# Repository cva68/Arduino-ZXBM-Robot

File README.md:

# Arduino ZXBM Robot
Chassis, PCB and Software to create an Arduino robot, including a custom motor driver shield based on the [ZXBM5210 motor driver](https://www.diodes.com/assets/Datasheets/products_inactive_data/ZXBM5210.pdf), and a chassis to hold two ["TT" geared DC motors](https://www.adafruit.com/product/3777). 

The Arduino shield design can be found in [hw](hw), and the robot chassis design can be found in [chassis](/chassis). Modules for interfacing with the shield can be found in [lib](/lib), and example control code is in [src](/src).

## Chassis
This chassis is specifically designed for the **Univeristy of Canterbury** Arduino Uno clone. The mount positions will need to be modified to be used with a standard Arduino Uno.

This is designed for 3D printing. Support will only be needed for the overhangs on the top of the chassis that are used to support the Arduino.

## Control Hardware

Designed in KiCad. [MotorDriverShield.kicad_pcb](hw/MotorDriverShield.kicad_pcb) and [MotorDriverShield.kicad_sch](hw/MotorDriverShield.kicad_sch) can be loaded into KiCad to modify the schematic or export Gerber files.

### Schematic

### PCB

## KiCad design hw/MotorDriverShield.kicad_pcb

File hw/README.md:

# Control Hardware

Designed in KiCad. [MotorDriverShield.kicad_pcb](MotorDriverShield.kicad_pcb) and [MotorDriverShield.kicad_sch](MotorDriverShield.kicad_sch) can be loaded into KiCad to modify the schematic or export Gerber files.

## Schematic

## PCB

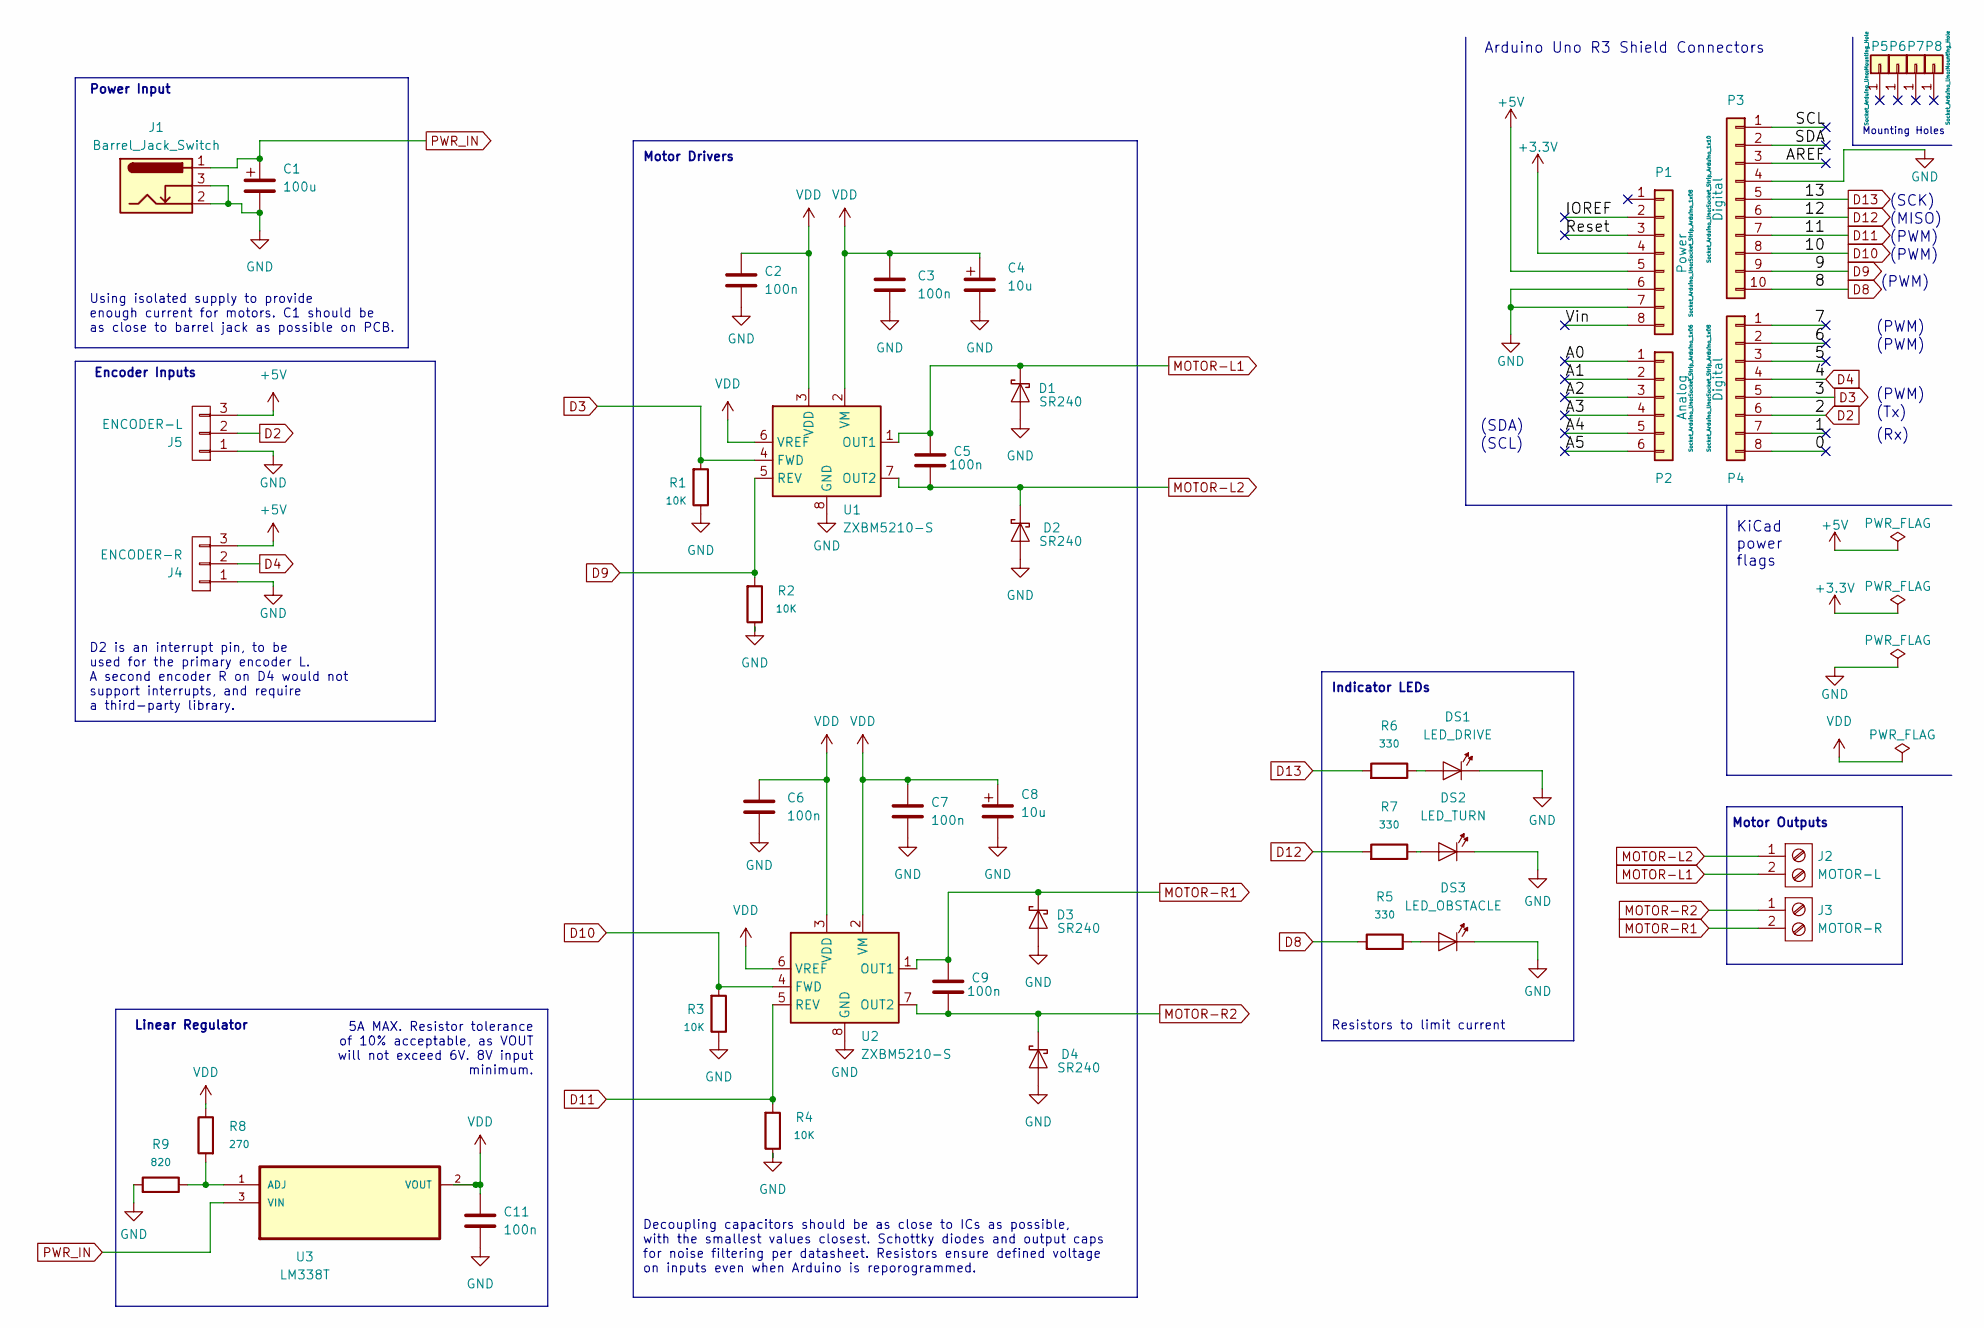
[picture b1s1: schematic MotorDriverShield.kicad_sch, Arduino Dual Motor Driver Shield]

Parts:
C1: 100u; CP_Radial_D8.0mm_P3.50mm
C2, C3, C5, C6, C7, C9, C11: 100n; C_Rect_L4.6mm_W3.0mm_P2.50mm_MKS02_FKP02
C4, C8: 10u; CP_Radial_D8.0mm_P3.50mm
D1, D2, D3, D4: SR240; D_DO-35_SOD27_P2.54mm_Vertical_AnodeUp
DS1: LED_DRIVE; LED_D5.0mm
DS2: LED_TURN; LED_D5.0mm
DS3: LED_OBSTACLE; LED_D5.0mm
J1: Barrel_Jack_Switch; BarrelJack_Horizontal
J2: MOTOR-L; TerminalBlock_Phoenix_MKDS-1,5-2-5.08_1x02_P5.08mm_Horizont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
J3: MOTOR-R; TerminalBlock_Phoenix_MKDS-1,5-2-5.08_1x02_P5.08mm_Horizont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
J4: ENCODER-R; PinHeader_1x03_P2.54mm_Vertical
J5: ENCODER-L; PinHeader_1x03_P2.54mm_Vertical
P1: Power; Socket_Strip_Arduino_1x08
P2: Analog; Socket_Strip_Arduino_1x06
P3: Digital; Socket_Strip_Arduino_1x10
P4: Digital; Socket_Strip_Arduino_1x08
P5, P6, P7, P8: CONN_01X01; Mounting_Hole
R1, R2, R3, R4: 10K; R_Axial_DIN0207_L6.3mm_D2.5mm_P7.62mm_Horizontal
R5, R6, R7: 330; R_Axial_DIN0207_L6.3mm_D2.5mm_P7.62mm_Horizontal
R8: 270; R_Axial_DIN0207_L6.3mm_D2.5mm_P7.62mm_Horizontal
R9: 820; R_Axial_DIN0207_L6.3mm_D2.5mm_P7.62mm_Horizontal
U1, U2: ZXBM5210-S; SOIC-8_3.9x4.9mm_P1.27mm
U3: LM338T; TO-220-3_Horizontal_TabDown

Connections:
+3.3V: P1.4
+5V: J4.3, J5.3, P1.5
/0: P4.8
/1: P4.7
/5: P4.3
/6: P4.2
/7: P4.1
/A0: P2.1
/A1: P2.2
/A2: P2.3
/A3: P2.4
/A4: P2.5
/A5: P2.6
/AREF: P3.3
/IOREF: P1.2
/Reset: P1.3
/SCL: P3.1
/SDA: P3.2
/Vin: P1.8
D2: J5.2, P4.6
D3: P4.5, R1.1, U1.4 (FWD)
D4: J4.2, P4.4
D8: P3.10, R5.1
D9: P3.9, R2.1, U1.5 (REV)
D10: P3.8, R3.1, U2.4 (FWD)
D11: P3.7, R4.1, U2.5 (REV)
D12: P3.6, R7.1
D13: P3.5, R6.1
GND: C1.2, C2.2, C3.2, C4.2, C6.2, C7.2, C8.2, C11.2, D1.2 (A), D2.2 (A), D3.2 (A), D4.2 (A), DS1.1 (K), DS2.1 (K), DS3.1 (K), J1.2, J1.3, J4.1, J5.1, P1.6, P1.7, P3.4, R1.2, R2.2, R3.2, R4.2, R9.1, U1.8 (GND), U2.8 (GND)
MOTOR-L1: C5.1, D1.1 (K), J2.2, U1.1 (OUT1)
MOTOR-L2: C5.2, D2.1 (K), J2.1, U1.7 (OUT2)
MOTOR-R1: C9.1, D3.1 (K), J3.2, U2.1 (OUT1)
MOTOR-R2: C9.2, D4.1 (K), J3.1, U2.7 (OUT2)
unnamed: DS1.2 (A), R6.2
unnamed: DS2.2 (A), R7.2
unnamed: DS3.2 (A), R5.2
unnamed: R8.1, R9.2, U3.1 (ADJ)
PWR_IN: C1.1, J1.1, U3.3 (VIN)
VDD: C2.1, C3.1, C4.1, C6.1, C7.1, C8.1, C11.1, R8.2, U1.2 (VM), U1.3 (VDD), U1.6 (VREF), U2.2 (VM), U2.3 (VDD), U2.6 (VREF), U3.2 (VOUT)

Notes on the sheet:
KiCad power flags
Motor Outputs
(Tx)
Decoupling capacitors should be as close to ICs as possible, with the smallest values closest. Schottky diodes and output caps for noise filtering per datasheet. Resistors ensure defined voltage on inputs even when Arduino is reporogrammed.
(SCK)
Encoder Inputs
Indicator LEDs
5A MAX. Resistor tolerance of 10% acceptable, as VOUT will not exceed 6V. 8V input minimum.
Using isolated supply to provide enough current for motors. C1 should be as close to barrel jack as possible on PCB.
(PWM)
(Rx)
Resistors to limit current
Arduino Uno R3 Shield Connectors
(SCL)
(MISO)
Mounting Holes
(SDA)
Linear Regulator
D2 is an interrupt pin, to be used for the primary encoder L. A second encoder R on D4 would not support interrupts, and require a third-party library.
Power Input
Motor Drivers

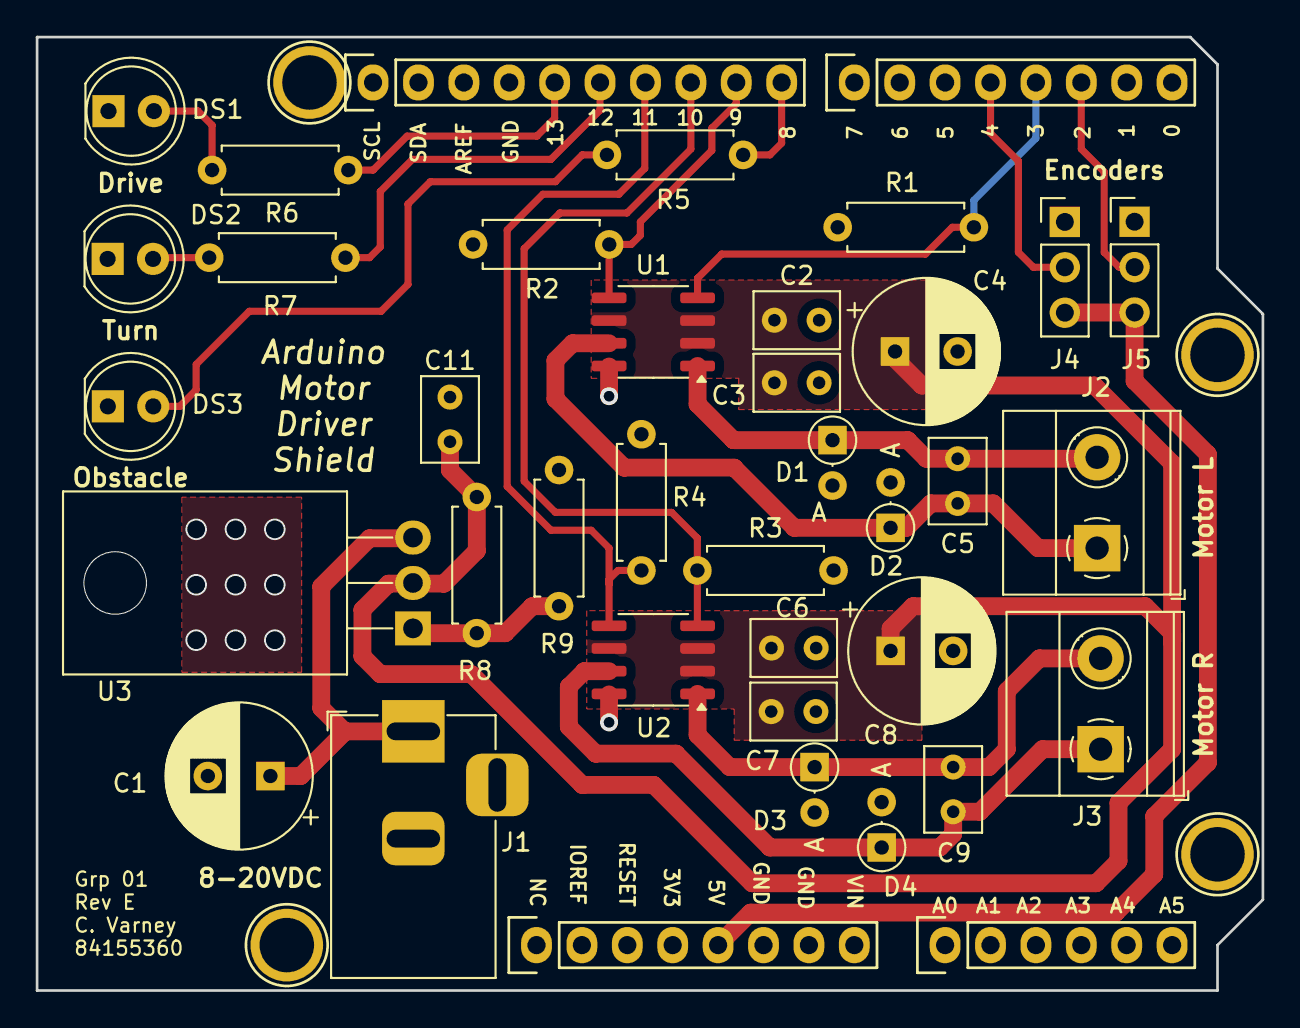
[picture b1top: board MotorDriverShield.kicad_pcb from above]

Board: 2 copper layers, 68.6 x 53.3 mm, 42 parts (0 on the bottom side), 21 nets.

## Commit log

2025-04-14 Added hardware and chassis
2025-04-14 Updated license, readme
